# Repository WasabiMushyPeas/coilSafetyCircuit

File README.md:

# Coil Safety Circuit :electric_plug:

## Introduction :wave:
This safety circuit uses an ESP32 C6 to detect temperature fluctuations or moisture build up on an electromagnet. It can shut off the coils via relay if needed. The ESP32 also hosts a network and webpage to monitor the status of the coils and set the temperature shut off threshold.

## Specifications :clipboard:
- **Power Supply:** USB-C cable to micro controller
- **Max Continuous Coil Power (Each coil):** 65v 5A
- **Max Burst Coil Power:** 65v 35A
- **Pump Power:** 12v 5A
- **Temperature Sensors:** 4 thermistors with an accuracy of ±0.25°C

## Webpage :computer:

This picture shows the default settings and appearance of the ESP32 webpage. The user can change the state of the coils and the pump with the three buttons in the top row. If a button is coloured red then that setting or component is off (no relay is open). All coils are off by default and the pump remains on. The user can also turn on and off temperature and moisture shut off with the buttons on the bottom row. It is also possible to change the temperature shut off threshold by clicking the plus or minus buttons on the temperature shut off button until the desired temperature is shown. The middle row show the current temperature average of all the thermistors and whether the moisture sensors are detecting water (0 being to water 1 being water). If the middle row cell is clicked or hovered over it displays more information about the sensors.

:warning: **Warning:** if the ESP32 crashes or loses power everything will be reset to default settings. :warning:

- **Default Settings:** Coils 1 and 2 are off, the pump is on, temperature shut off is on, moisture shut off is off, and the temperature shut off threshold is 60°C.

## Network :satellite:

The webpage can be accessed by connect to the ESP32 network and typing the IP address of the ESP32 into a web browser. The IP address is displayed on the serial monitor when the ESP32 is booting up.

The network name is:
```
ESP32-Access-Point
```

The password is:
```
rydberg12
```

The default IP address is:

```
192.168.4.1
```

## LED Indicators :bulb:
- **Green LED:** Normal operation and coils are off
- **Red LED:** Temperature shut off is active
- **Orange LED:** Moisture shut off is active
- **Blue LED:** Coils are on
- **No LED:** Something is very wrong with the ESP32

## Parts List :moneybag:

| Part                                                                                                               | Quantity | Price  |
| ------------------------------------------------------------------------------------------------------------------ | -------- | ------ |
| [ESP32 C6 DEV](https://www.digikey.com/en/products/detail/espressif-systems/ESP32-C6-DEVKITM-1-N4/18667011)        | 1        | $8.00  |
| [Thermistor](https://www.digikey.com/en/products/detail/adafruit-industries-llc/4890/13982731)                     | 4        | $4.75  |
| [Water Sensor](https://www.digikey.com/en/products/detail/adafruit-industries-llc/4965/14302510)                   | 2        | $3.90  |
| [Coil Relay](https://www.digikey.com/en/products/detail/american-zettler/AZDC007-1AE-12D/22050421)                 | 2        | $11.78 |
| [Pump Relay](https://www.digikey.com/en/products/detail/american-zettler/AZ943-1CH-12DE/12171590)                  | 1        | $0.95  |
| [Barrel Connector](https://www.digikey.com/en/products/detail/cui-devices/PJ-037AH/1644547)                        | 1        | $0.74  |
| [Barrel Connector Cable](https://www.digikey.com/en/products/detail/tensility-international-corp/10-01062/3507709) | 1        | $1.93  |
| [2 Pin Terminal](https://www.digikey.com/en/products/detail/cui-devices/TB002-500-02BE/10064069)                   | 3        | $1.68  |
| [6 Pin Terminal](https://www.digikey.com/en/products/detail/cui-devices/TB003-500-P06BE/100640891)                 | 1        | $0.80  |
| [8 Pin Terminal](https://www.digikey.com/en/products/detail/cui-devices/TB001-500-08BE/10064064)                   | 1        | $1.29  |
| [10k Resistor](https://www.digikey.com/en/products/detail/panasonic-electronic-components/ERA-6AEB103V/1465773)    | 10       | $0.99  |
| [DC to DC Converter](https://www.digikey.com/en/products/detail/gaptec-electronic/1S4E-0312S1U/13692037)           | 3        | $8.31  |
| [PCB](https://jlcpcb.com/)                                                                                         | 1        | ~$5    |
| Total (without taxes + shipping)                                                                                   |          | $49.82 |

## Notes :notebook:

:heavy_exclamation_mark: Some things that need to be done :heavy_exclamation_mark:
- Thermistors need to be calibrated
- Code has not been tested with the PCB yet
- PCB has not been tested yet

Some things that could be added or changed:
- Better website with websockets
- A way to save settings and not reset on power loss
- When connected to the network the control page should pop up automatically using captive portals
- Add a way for ESP32 to get power from the pump power supply
- connect the ESP32 to the lab warning system and trigger when the coils get too hot or wet
- Have the Website accessable out of the lab by having the ESP32 connect to the internet and port forward the website port

## More Information :mag_right:

[Wifi Tutorial](https://randomnerdtutorials.com/esp32-access-point-ap-web-server/)
[Thermistor Tutorial](https://learn.adafruit.com/thermistor/using-a-thermistor)

If you have any questions or suggestions start an issue [here](https://github.com/WasabiMushyPeas/coilSafetyCircuit/issues/new)

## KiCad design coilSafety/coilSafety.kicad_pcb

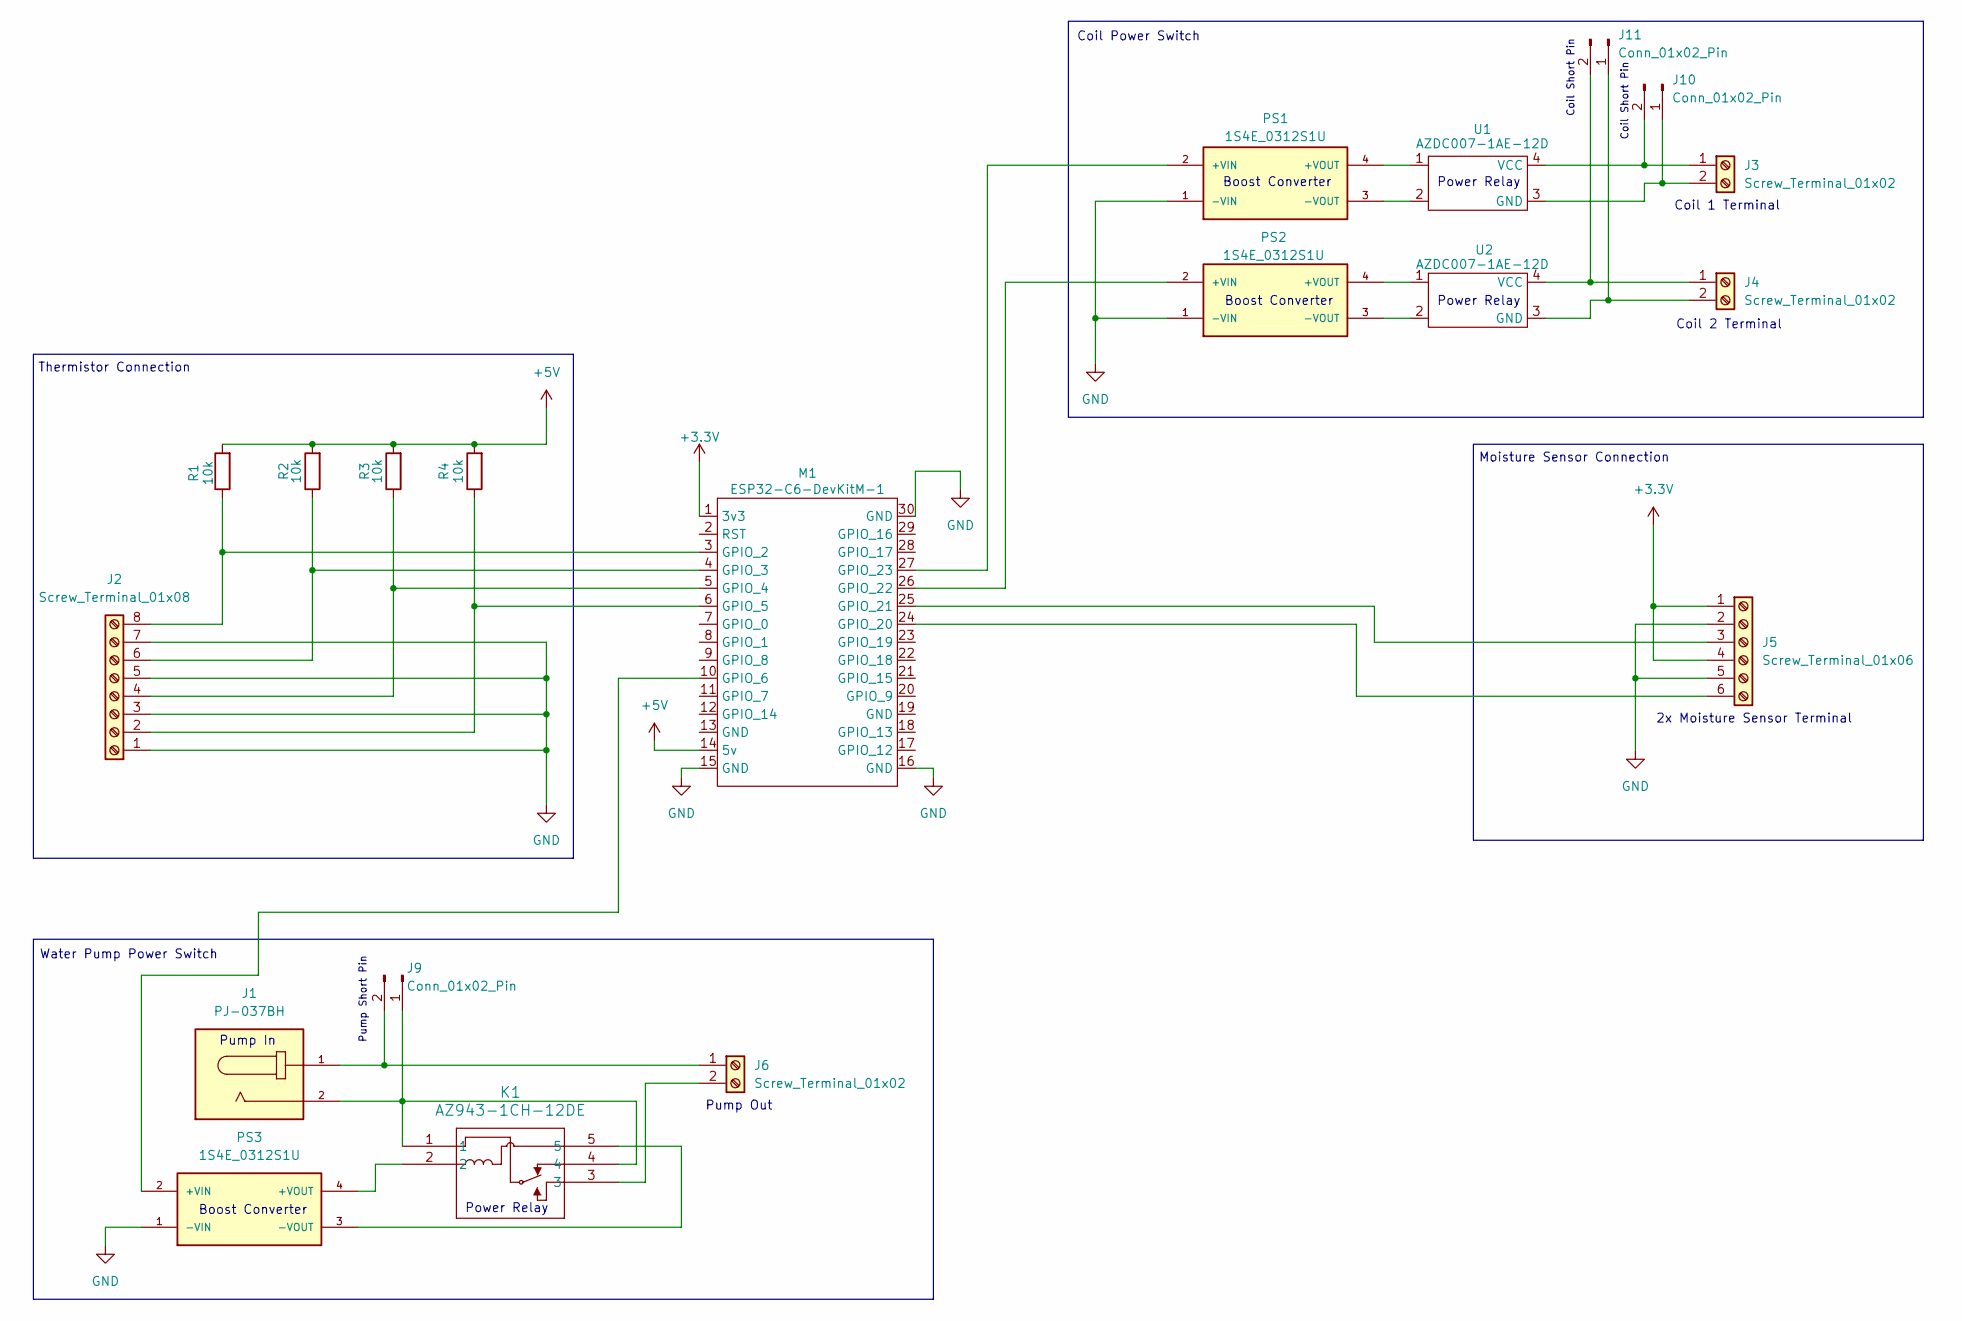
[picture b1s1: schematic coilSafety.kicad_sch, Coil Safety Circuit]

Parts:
J1: PJ-037BH; CUI_PJ-037BH
J2: Screw_Terminal_01x08; CUI_TB001-500-08BE
J3, J4, J6: Screw_Terminal_01x02; CUI_TB002-500-02BE
J5: Screw_Terminal_01x06; CUI_TB003-500-P06BE
J9, J10, J11: Conn_01x02_Pin; TerminalBlock_bornier-2_P5.08mm
K1: AZ943-1CH-12DE
M1: ESP32-C6-DevKitM-1
PS1, PS2, PS3: 1S4E_0312S1U; CONV_1S4E_0312S1U
R1, R2, R3, R4: 10k; R_0805_2012Metric
U1, U2: AZDC007-1AE-12D

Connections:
+3.3V: J5.1, J5.4, M1.1 (3v3)
+5V: M1.14 (5v), R1.2, R2.2, R3.2, R4.2
GND: J2.1, J2.3, J2.5, J2.7, J5.2, J5.5, M1.15 (GND), M1.16 (GND), M1.30 (GND), PS1.1 (-VIN), PS2.1 (-VIN), PS3.1 (-VIN)
unnamed: J2.2, M1.6 (GPIO_5), R4.1
unnamed: J2.4, M1.5 (GPIO_4), R3.1
unnamed: J2.6, M1.4 (GPIO_3), R2.1
unnamed: J2.8, M1.3 (GPIO_2), R1.1
unnamed: J5.3, M1.25 (GPIO_21)
unnamed: J5.6, M1.24 (GPIO_20)
unnamed: J1.1, J6.1, J9.2
unnamed: J6.2, K1.3
unnamed: J1.2, J9.1, K1.1, K1.4
unnamed: J3.2, J10.1, U1.3 (GND)
unnamed: J3.1, J10.2, U1.4 (VCC)
unnamed: J4.2, J11.1, U2.3 (GND)
unnamed: J4.1, J11.2, U2.4 (VCC)
unnamed: M1.10 (GPIO_6), PS3.2 (+VIN)
unnamed: M1.26 (GPIO_22), PS2.2 (+VIN)
unnamed: M1.27 (GPIO_23), PS1.2 (+VIN)
unnamed: PS1.4 (+VOUT), U1.1
unnamed: PS1.3 (-VOUT), U1.2
unnamed: PS2.4 (+VOUT), U2.1
unnamed: PS2.3 (-VOUT), U2.2
unnamed: K1.2, PS3.4 (+VOUT)
unnamed: K1.5, PS3.3 (-VOUT)

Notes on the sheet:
Coil Short Pin
Coil 1 Terminal
Power Relay
Pump Out
Pump In
Water Pump Power Switch
Coil 2 Terminal
2x Moisture Sensor Terminal
Boost Converter
Pump Short Pin
Coil Power Switch
Moisture Sensor Connection
Thermistor Connection

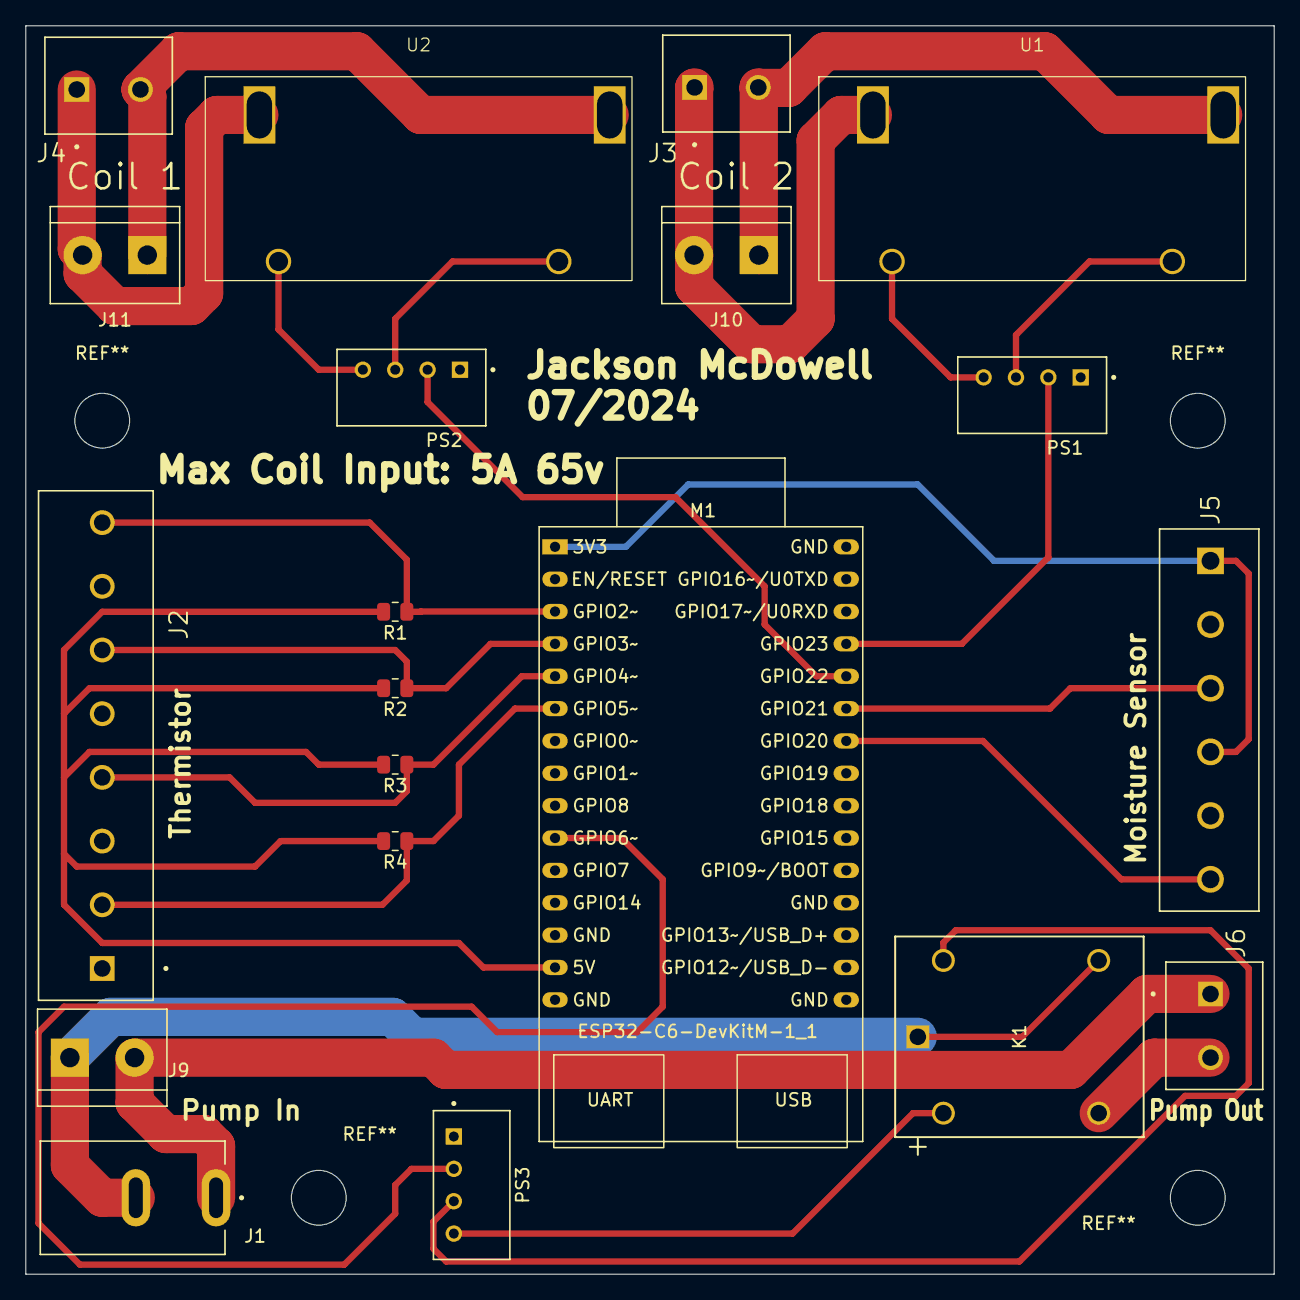
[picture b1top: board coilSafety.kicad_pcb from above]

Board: 2 copper layers, 98.0 x 98.0 mm, 20 parts (0 on the bottom side), 25 nets.

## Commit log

2024-07-16 Jason's Updates
2024-07-16 auto gen
2024-07-16 clean up
2024-07-16 last commit before Jason
2024-07-16 v2 schematic complete
2024-07-16 Working on PCB
2024-07-17 final commit
2024-07-17 fixed trace and text
2024-07-17 Update README.md with specifications and parts list
2024-07-17 Update README.md with additional information about the ESP32 C6 and coil monitoring
2024-07-17 Update README.md with coil safety circuit details
2024-07-17 production
2024-07-19 quote
2024-07-19 Added ESP32 code
2024-07-19 Add ESP32 web server code with AP functionality
2024-07-19 move AP web server code and add all switches
2024-07-24 Test page finished
2024-07-24 Refactor test.html to update moisture pump/coil labels and remove commented code
2024-07-24 chore: Add endpoint handlers for controlling temperature and pump/moisture coils
2024-07-24 feat: Add endpoint handlers for controlling temperature and pump/moisture coils
2024-07-24 chore: Refactor test.html to update moisture pump/coil labels and remove commented code
2024-07-24 Refactor moisture reading logic to use boolean values instead of string comparison
2024-07-25 feat: Add temperature sensors to parts list
2024-07-25 add: Add website pics
2024-07-25 feat: Add webpage screenshot to README.md
2024-07-25 Update coil shutoff temperature to 65 degrees
2024-07-25 update: newer pics
2024-07-25 Update default settings and appearance of ESP32 webpage
2024-07-25 chore: Update PCB link, network information, default settings, and appearance of ESP32 webpage
2024-07-25 chore: Update notes in README.md
